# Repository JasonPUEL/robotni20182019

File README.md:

# RobotNI

Le robot aura pour nouvel objectif de chercher son chemin dans un environnement inconnu. Il devra le cartographier pour « faire des livraison/ trie de colis » en fonction de contrainte prédéfini.
Apres définition de ces contraintes le robot pourra être parfaitement autonome, bien qu’un retour d’informations vers l’utilisateur soit possible (retour vidéo/informations sur la carte découverte).
Les contraintes pourront être de chercher « colis », les trier et éventuellement de déposer les « colis » à un endroit prédéfinit.

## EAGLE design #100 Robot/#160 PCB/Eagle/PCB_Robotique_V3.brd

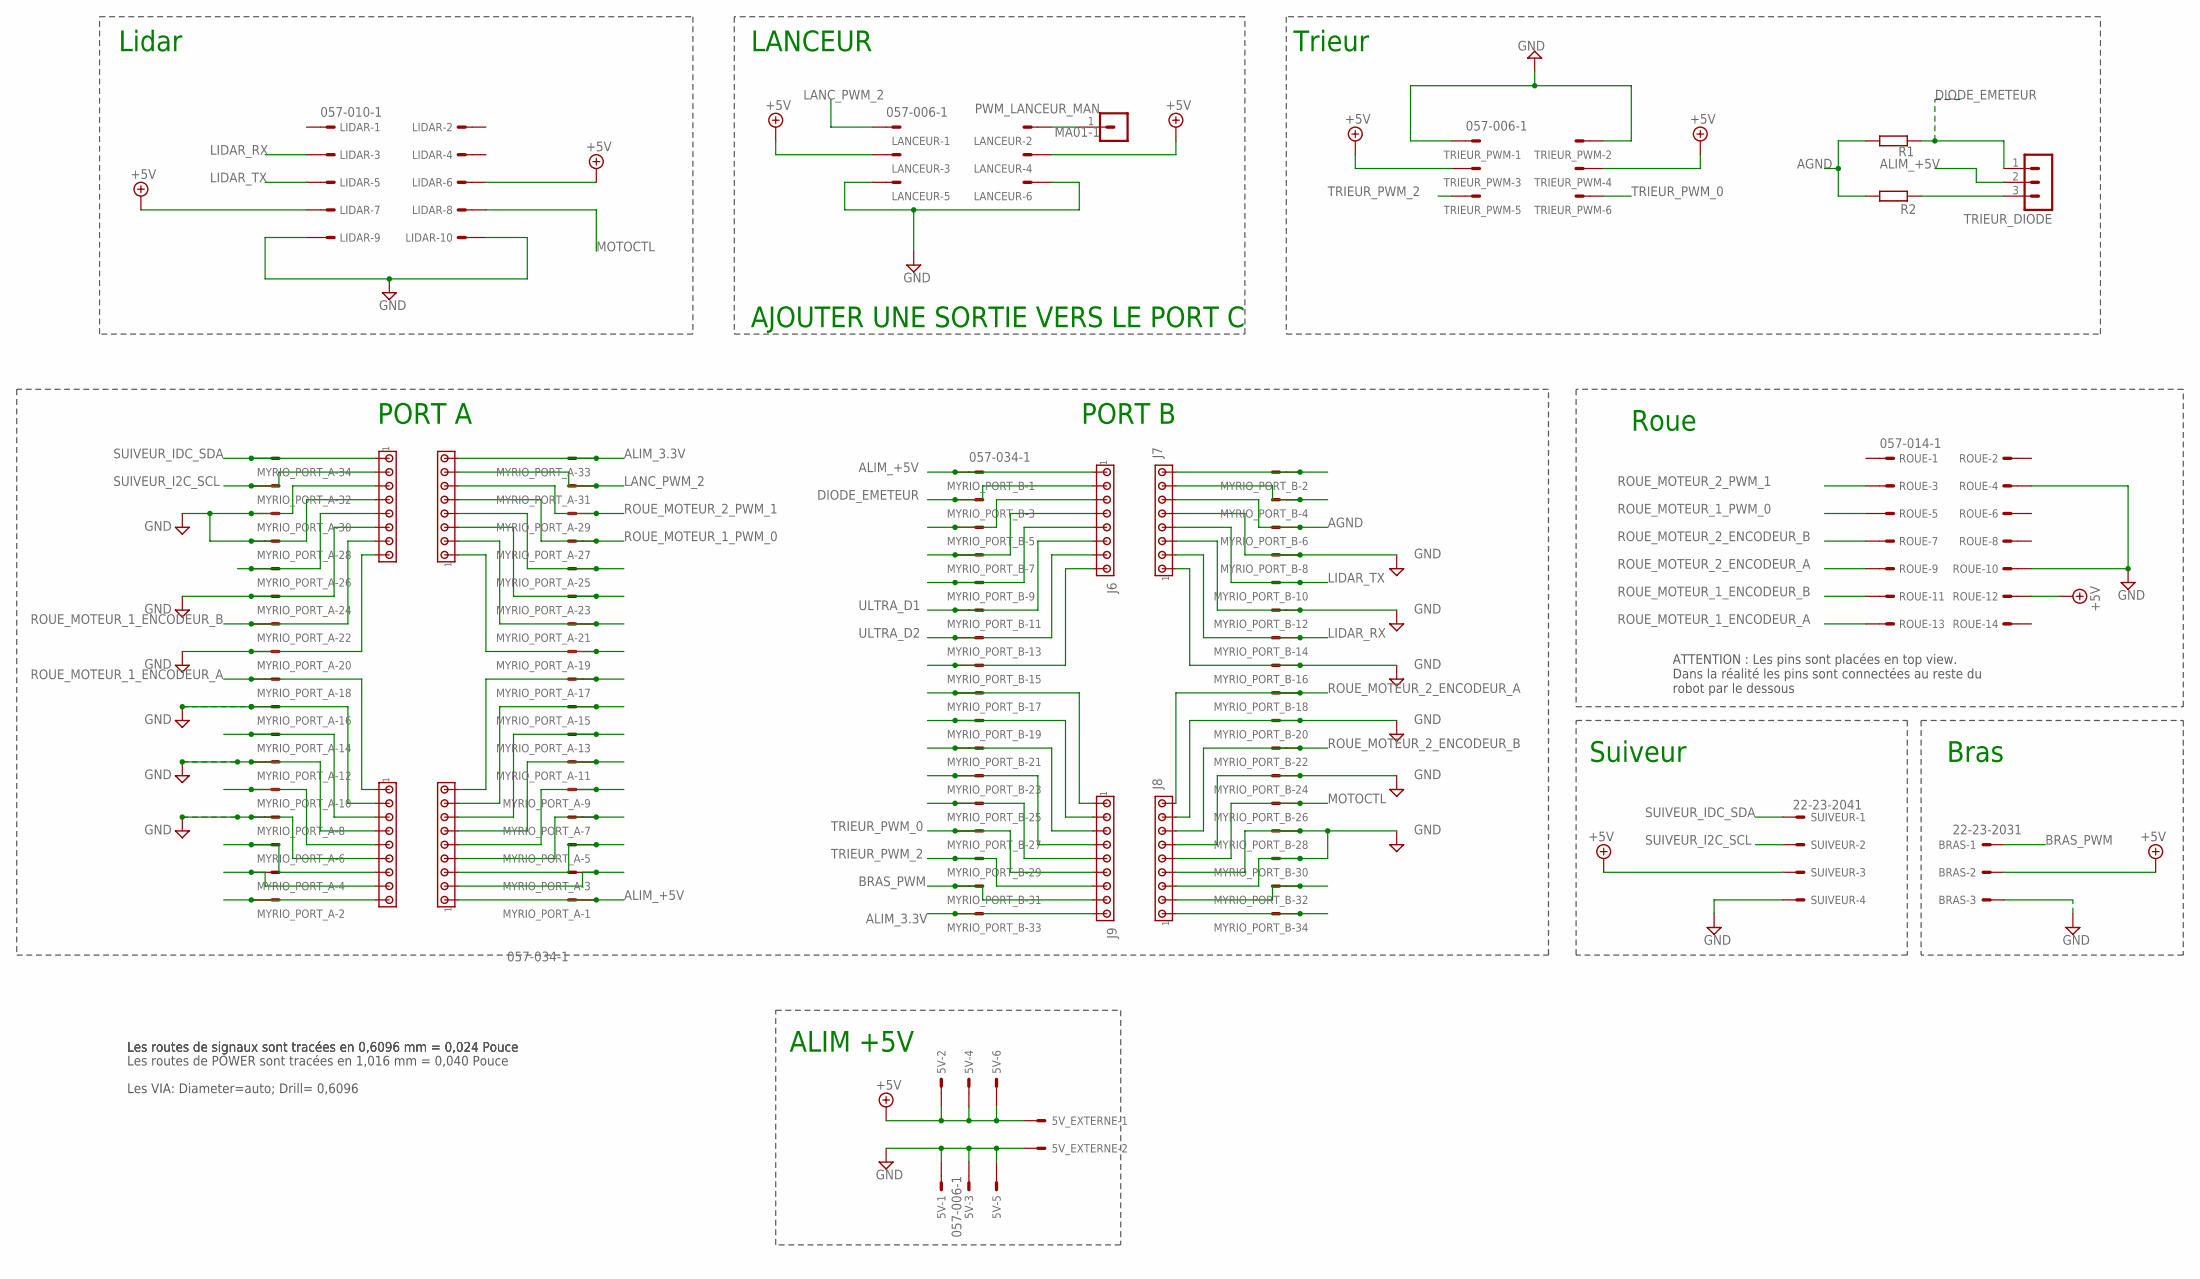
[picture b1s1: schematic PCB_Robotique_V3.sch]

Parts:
5V: 057-006-1
5V_EXTERNE: KK-156-2
BRAS: 22-23-2031
J2, J3, J6, J7: MTA08-100; 10X08MTA
J4, J5, J8, J9: MTA09-100; 10X09MTA
LANCEUR: 057-006-1
LIDAR: 057-010-1
MYRIO_PORT_A: 057-034-1
MYRIO_PORT_B: 057-034-1
PWM_LANCEUR_MAN: MA01-1
R1: 15K; R
R2: 180; R
ROUE: 057-014-1
SUIVEUR: 22-23-2041
TRIEUR_DIODE: MA03-1
TRIEUR_PWM: 057-006-1

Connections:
4B: J7.7, MYRIO_PORT_B.4
+5V: 5V.2, 5V.4, 5V.6, 5V_EXTERNE.1, BRAS.2, LANCEUR.3, LANCEUR.4, LIDAR.6, LIDAR.7, ROUE.12, SUIVEUR.3, TRIEUR_PWM.3, TRIEUR_PWM.4
AGND: J7.6, MYRIO_PORT_B.6, R1.1, R2.2
ALIM_3.3V: J3.8, J9.9, MYRIO_PORT_A.33, MYRIO_PORT_B.33
ALIM_+5V: J4.1, J6.1, MYRIO_PORT_A.1, MYRIO_PORT_B.1, TRIEUR_DIODE.2
BRAS_PWM: BRAS.1, J9.8, MYRIO_PORT_B.31
DIODE: R2.1, TRIEUR_DIODE.3
DIODE_EMETEUR: J6.2, MYRIO_PORT_B.3, R1.2, TRIEUR_DIODE.1
GND: 5V.1, 5V.3, 5V.5, 5V_EXTERNE.2, BRAS.3, J2.3, J2.4, J2.6, J2.8, J5.2, J5.4, J5.6, J7.1, J7.3, J7.5, J8.3, J8.4, J8.6, J8.8, LANCEUR.5, LANCEUR.6, LIDAR.9, LIDAR.10, MYRIO_PORT_A.8, MYRIO_PORT_A.12, MYRIO_PORT_A.16, MYRIO_PORT_A.20, MYRIO_PORT_A.24, MYRIO_PORT_A.28, MYRIO_PORT_A.30, MYRIO_PORT_B.8, MYRIO_PORT_B.12, MYRIO_PORT_B.16, MYRIO_PORT_B.20, MYRIO_PORT_B.24, MYRIO_PORT_B.28, MYRIO_PORT_B.30, ROUE.4, ROUE.10, SUIVEUR.4, TRIEUR_PWM.1, TRIEUR_PWM.2
LANC_PWM_2: J3.7, LANCEUR.1, MYRIO_PORT_A.31
LIDAR_RX: J7.2, LIDAR.3, MYRIO_PORT_B.14
LIDAR_TX: J7.4, LIDAR.5, MYRIO_PORT_B.10
MOTOCTL: J8.5, LIDAR.8, MYRIO_PORT_B.26
unnamed: J2.5, MYRIO_PORT_A.26
unnamed: J7.8, MYRIO_PORT_B.2
unnamed: J5.8, MYRIO_PORT_A.4
unnamed: J5.9, MYRIO_PORT_A.2
unnamed: J3.4, MYRIO_PORT_A.25
unnamed: J3.3, MYRIO_PORT_A.23
unnamed: J3.2, MYRIO_PORT_A.21
unnamed: J3.1, MYRIO_PORT_A.19
unnamed: J4.9, MYRIO_PORT_A.17
unnamed: J4.8, MYRIO_PORT_A.15
unnamed: J4.7, MYRIO_PORT_A.13
unnamed: J4.6, MYRIO_PORT_A.11
unnamed: J4.5, MYRIO_PORT_A.9
unnamed: J4.4, MYRIO_PORT_A.7
unnamed: J4.3, MYRIO_PORT_A.5
unnamed: J4.2, MYRIO_PORT_A.3
unnamed: J8.2, MYRIO_PORT_B.32
unnamed: J8.1, MYRIO_PORT_B.34
unnamed: J9.5, MYRIO_PORT_B.25
unnamed: J9.4, MYRIO_PORT_B.23
unnamed: J9.3, MYRIO_PORT_B.21
unnamed: J9.2, MYRIO_PORT_B.19
unnamed: J9.1, MYRIO_PORT_B.17
unnamed: J6.8, MYRIO_PORT_B.15
unnamed: J6.5, MYRIO_PORT_B.9
unnamed: J6.4, MYRIO_PORT_B.7
unnamed: J6.3, MYRIO_PORT_B.5
unnamed: J5.7, MYRIO_PORT_A.6
PWM_LANCEUR_MAN: LANCEUR.2, PWM_LANCEUR_MAN.1
ROUE_MOTEUR_1_ENCODEUR_A: J5.1, MYRIO_PORT_A.18, ROUE.13
ROUE_MOTEUR_1_ENCODEUR_B: J2.7, MYRIO_PORT_A.22, ROUE.11
ROUE_MOTEUR_1_PWM_0: J3.5, MYRIO_PORT_A.27, ROUE.5
ROUE_MOTEUR_2_ENCODEUR_A: J8.9, MYRIO_PORT_B.18, ROUE.9
ROUE_MOTEUR_2_ENCODEUR_B: J8.7, MYRIO_PORT_B.22, ROUE.7
ROUE_MOTEUR_2_PWM_1: J3.6, MYRIO_PORT_A.29, ROUE.3
SDFSDFSGD: J5.5, MYRIO_PORT_A.10
SDSSDFD: J5.3, MYRIO_PORT_A.14
SUIVEUR_I2C_SCL: J2.2, MYRIO_PORT_A.32, SUIVEUR.2
SUIVEUR_I2C_SDA: J2.1, MYRIO_PORT_A.34, SUIVEUR.1
TRIEUR_PWM_0: J9.6, MYRIO_PORT_B.27, TRIEUR_PWM.6
TRIEUR_PWM_2: J9.7, MYRIO_PORT_B.29, TRIEUR_PWM.5
ULTRA_D1: J6.6, MYRIO_PORT_B.11
ULTRA_D2: J6.7, MYRIO_PORT_B.13

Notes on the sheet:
Roue
Suiveur
PORT A
PORT B
LANCEUR
Trieur
ALIM +5V
Bras
AJOUTER UNE SORTIE VERS LE PORT C
Lidar
ATTENTION : Les pins sont placées en top view. Dans la réalité les pins sont connectées au reste du robot par le dessous
Les routes de signaux sont tracées en 0,6096 mm = 0,024 Pouce
Les VIA: Diameter=auto; Drill= 0,6096
Les routes de POWER sont tracées en 1,016 mm = 0,040 Pouce

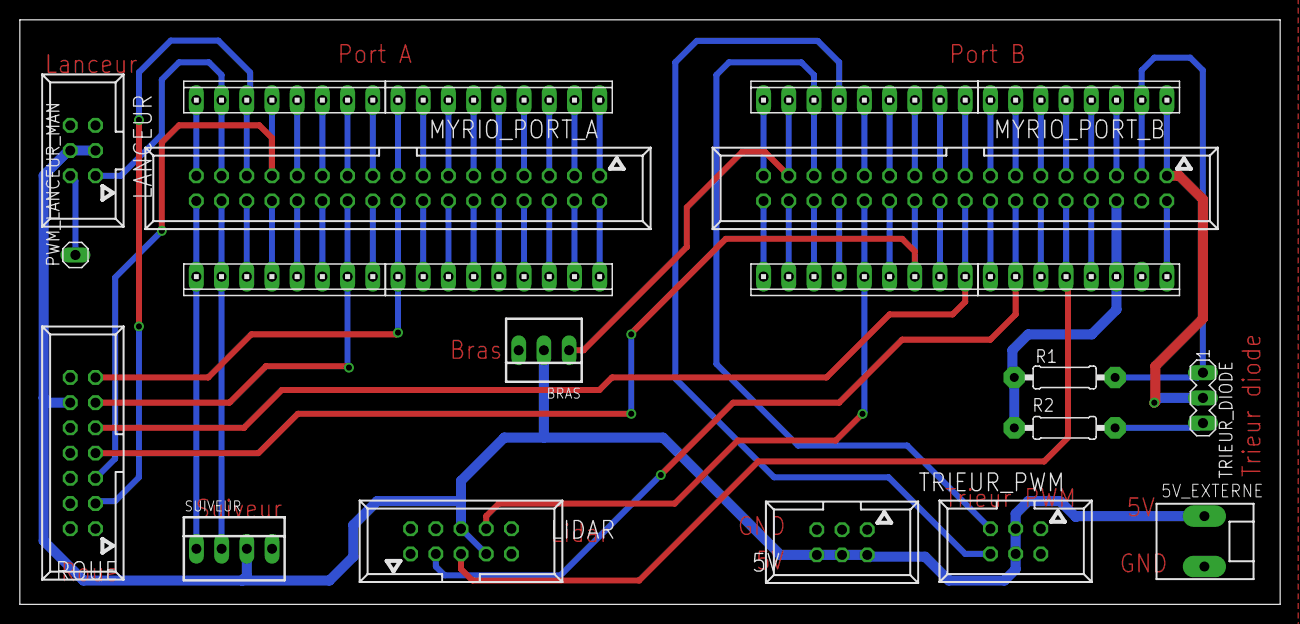
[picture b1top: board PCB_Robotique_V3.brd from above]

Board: 2 copper layers, 127.0 x 58.9 mm, 22 parts (0 on the bottom side), 56 nets.

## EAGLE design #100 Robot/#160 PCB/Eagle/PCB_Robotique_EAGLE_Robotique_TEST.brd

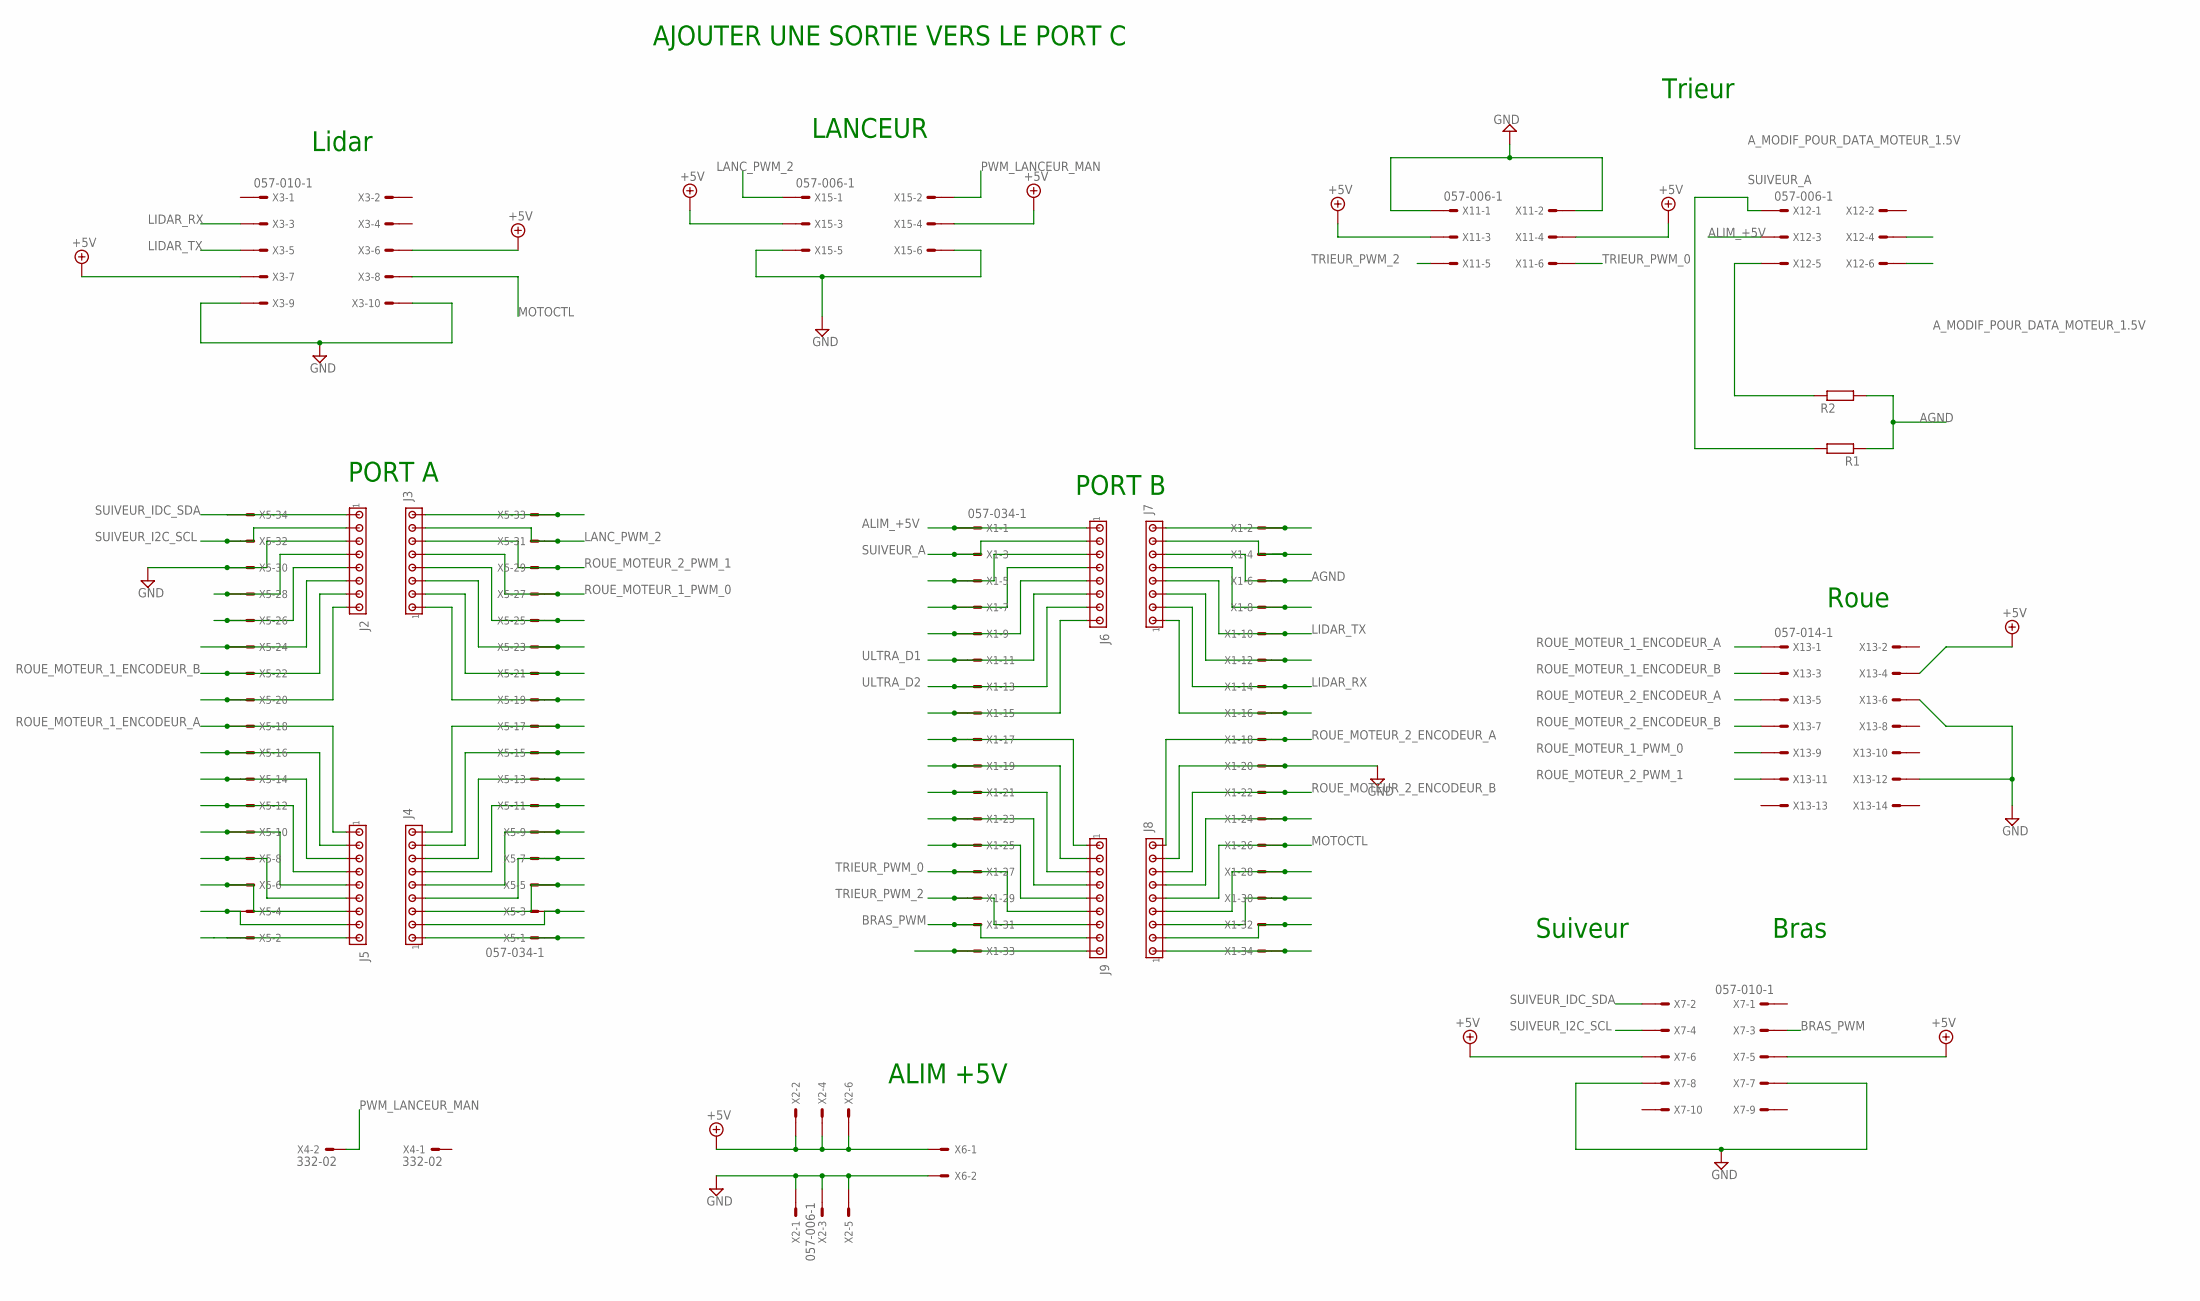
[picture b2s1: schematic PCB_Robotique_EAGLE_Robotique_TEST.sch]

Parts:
J2, J3, J6, J7: MTA08-100; 10X08MTA
J4, J5, J8, J9: MTA09-100; 10X09MTA
R1, R2: R1/4W; R
X1, X5: 057-034-1
X2, X11, X12, X15: 057-006-1
X3, X7: 057-010-1
X4: 332-02
X6: KK-156-2
X13: 057-014-1

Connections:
4B: J7.7, X1.4
+5V: X2.2, X2.4, X2.6, X3.6, X3.7, X6.1, X7.5, X7.6, X11.3, X11.4, X13.4, X15.3, X15.4
AGND: J7.6, R1.1, R2.2, X1.6
ALIM_+5V: J6.1, X1.1, X12.3
A_MODIF_POUR_DATA_MOTEUR_1.5V: R2.1, X12.5
BRAS_PWM: J9.8, X1.31, X7.3
GND: J2.3, J8.8, X1.20, X2.1, X2.3, X2.5, X3.9, X3.10, X5.30, X6.2, X7.7, X7.8, X11.1, X11.2, X13.6, X13.12, X15.5, X15.6
LANC_PWM_2: J3.7, X5.31, X15.1
LIDAR_RX: J7.2, X1.14, X3.3
LIDAR_TX: J7.4, X1.10, X3.5
MOTOCTL: J8.5, X1.26, X3.8
unnamed: J2.4, X5.28
unnamed: J2.5, X5.26
unnamed: J2.6, X5.24
unnamed: J5.2, X5.16
unnamed: J7.8, X1.2
unnamed: J5.4, X5.12
unnamed: J2.8, X5.20
unnamed: J5.6, X5.8
unnamed: J5.8, X5.4
unnamed: J5.9, X5.2
unnamed: J3.8, X5.33
unnamed: J3.4, X5.25
unnamed: J3.3, X5.23
unnamed: J3.2, X5.21
unnamed: J3.1, X5.19
unnamed: J4.9, X5.17
unnamed: J7.5, X1.8
unnamed: J7.3, X1.12
unnamed: J4.8, X5.15
unnamed: J4.7, X5.13
unnamed: J4.6, X5.11
unnamed: J4.5, X5.9
unnamed: J4.4, X5.7
unnamed: J4.3, X5.5
unnamed: J4.2, X5.3
unnamed: J4.1, X5.1
unnamed: J7.1, X1.16
unnamed: J8.6, X1.24
unnamed: J8.4, X1.28
unnamed: J8.3, X1.30
unnamed: J8.2, X1.32
unnamed: J8.1, X1.34
unnamed: J9.9, X1.33
unnamed: J9.5, X1.25
unnamed: J9.4, X1.23
unnamed: J9.3, X1.21
unnamed: J9.2, X1.19
unnamed: J9.1, X1.17
unnamed: J6.8, X1.15
unnamed: J6.5, X1.9
unnamed: J6.4, X1.7
unnamed: J6.3, X1.5
unnamed: J5.7, X5.6
PWM_LANCEUR_MAN: X4.2, X15.2
ROUE_MOTEUR_1_ENCODEUR_A: J5.1, X5.18, X13.1
ROUE_MOTEUR_1_ENCODEUR_B: J2.7, X5.22, X13.3
ROUE_MOTEUR_1_PWM_0: J3.5, X5.27, X13.9
ROUE_MOTEUR_2_ENCODEUR_A: J8.9, X1.18, X13.5
ROUE_MOTEUR_2_ENCODEUR_B: J8.7, X1.22, X13.7
ROUE_MOTEUR_2_PWM_1: J3.6, X5.29, X13.11
SDFSDFSGD: J5.5, X5.10
SDSSDFD: J5.3, X5.14
SUIVEUR_A: J6.2, R1.2, X1.3, X12.1
SUIVEUR_I2C_SCL: J2.2, X5.32, X7.4
SUIVEUR_IDC_SDA: J2.1, X5.34, X7.2
TRIEUR_PWM_0: J9.6, X1.27, X11.6
TRIEUR_PWM_2: J9.7, X1.29, X11.5
ULTRA_D1: J6.6, X1.11
ULTRA_D2: J6.7, X1.13

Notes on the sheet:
Roue
Suiveur
PORT A
PORT B
LANCEUR
Trieur
ALIM +5V
Bras
AJOUTER UNE SORTIE VERS LE PORT C
Lidar

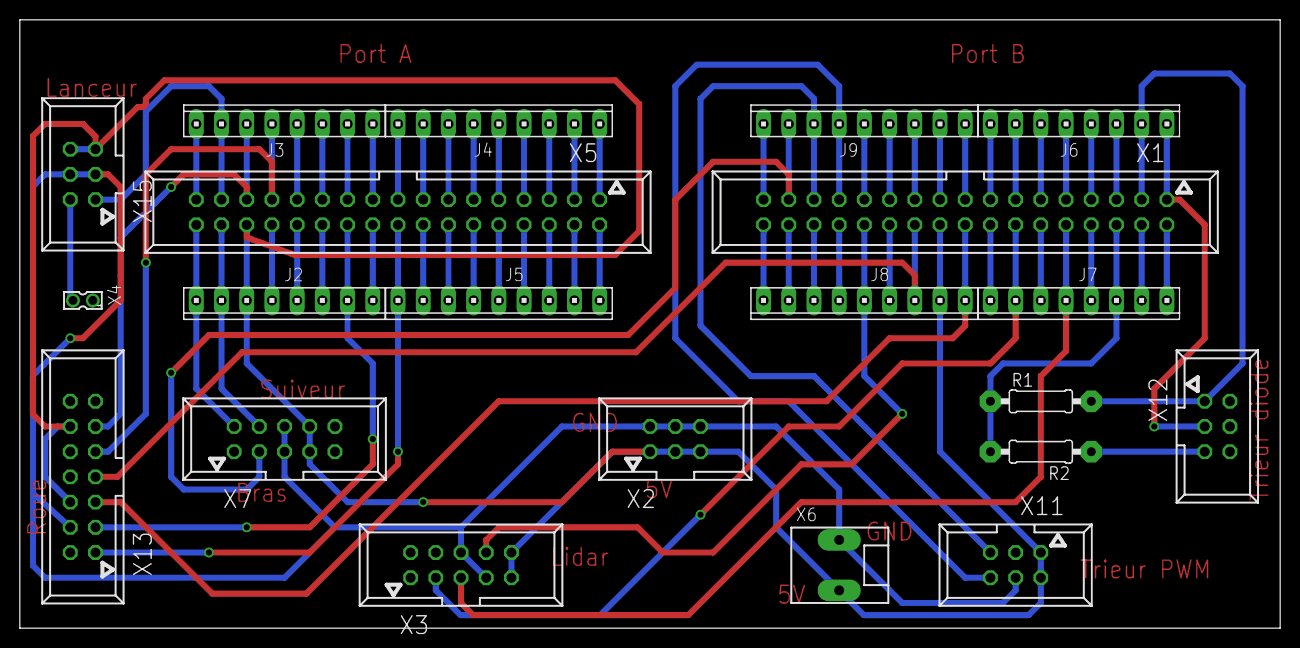
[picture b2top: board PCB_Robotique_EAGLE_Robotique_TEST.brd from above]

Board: 2 copper layers, 127.0 x 61.3 mm, 21 parts (0 on the bottom side), 70 nets.

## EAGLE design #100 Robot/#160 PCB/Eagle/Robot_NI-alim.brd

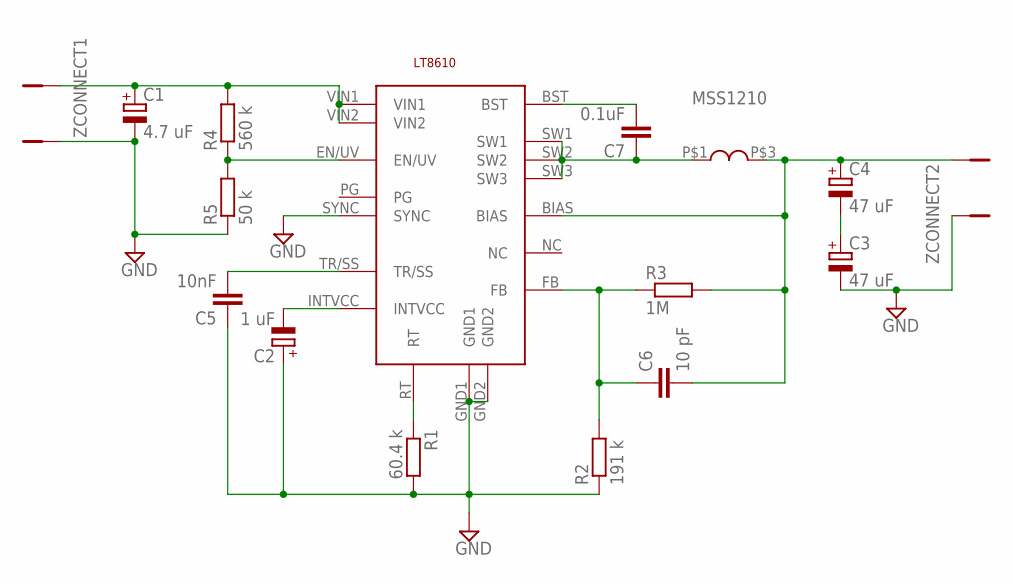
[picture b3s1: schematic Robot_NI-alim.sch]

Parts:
C1: 4.7 uF; C-POL5MM
C2: 1 uF; C-POL5MM
C3, C4: 47 uF; C-POL5MM
C5: 10nF; C0805
C6: 10 pF; C0805
C7: 0.1uF; C0805
R1: 60.4 k; R0805
R2: 191 k; R0805
R3: 1M; R0805
R4: 560 k; R0805
R5: 50 k; R0805
U$1: MSS1210
U$2: LT8610AC
ZCONNECT1, ZCONNECT2: LED5MM

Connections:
GND: C1.-, C2.+, C3.-, C5.1, R1.2, R2.1, R5.1, U$2.GND1, U$2.GND2, U$2.SYNC, ZCONNECT1.K (C), ZCONNECT2.A
unnamed: C1.+, R4.2, U$2.VIN1, U$2.VIN2, ZCONNECT1.A
unnamed: R4.1, R5.2, U$2.EN/UV
unnamed: C5.2, U$2.TR/SS
unnamed: C2.-, U$2.INTVCC
unnamed: C3.+, C4.-
unnamed: R1.1, U$2.RT
unnamed: C7.1, U$1.P$1, U$2.SW1, U$2.SW2, U$2.SW3
unnamed: C7.2, U$2.BST
unnamed: C4.+, C6.2, R3.2, U$1.P$3, U$2.BIAS, ZCONNECT2.K (C)
unnamed: C6.1, R2.2, R3.1, U$2.FB

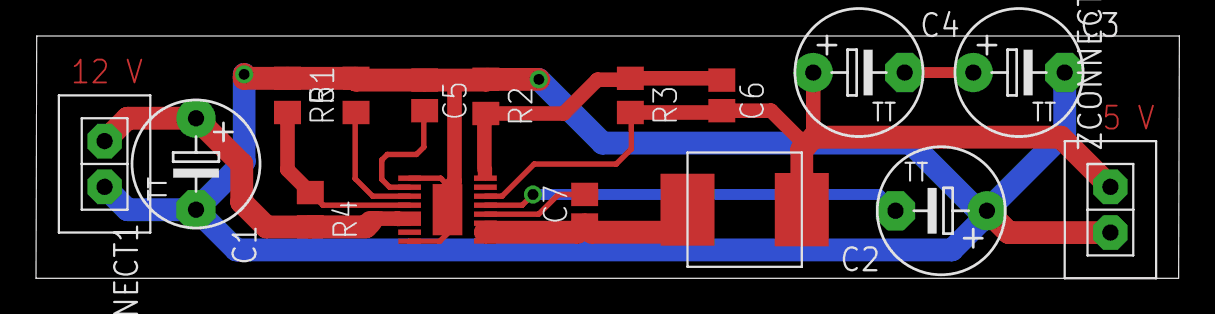
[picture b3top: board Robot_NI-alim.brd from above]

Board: 2 copper layers, 63.5 x 13.5 mm, 16 parts (0 on the bottom side), 11 nets.

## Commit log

2019-03-14 explication labview
2019-03-14 code + datasheets
2019-03-15 trieur de balles svg + code audio et video raspberry
2019-03-15 lcd library
2019-03-15 Boitier Raspberry
    Upload du fichier de découpe laser + Datasheet
2019-03-15 New Getion de fichiers
2019-03-15 Importation des fichiers M2
2019-03-21 Upload Datasheet Raspberry PI
2019-03-29 Push Regle 2018
2019-04-11 Update Weekly
2019-04-25 Update code Labview
2019-04-29 Update code Labview
    RT_Sceaux
2019-04-29 Datasheet diode + lanceur_RT
2019-04-30 Update code Ladview
2019-04-30 datasheet servo trappe
2019-05-02 RT sceaux/avance/recule/lanceur
2019-05-02 RT lanceur
2019-05-02 RT_trieur_balles
2019-05-02 update RT
2019-05-06 Doc code Labview
2019-05-09 Information Pitch
2019-05-09 sous_vi_RT_lanceur
    ajout def type enum_lanceur
2019-05-09 update virage RT
2019-05-12 RE Update code Labview
2019-05-13 Update Code Labview
    tout marche sauf trieur
2019-05-15 PCB V3 + Weekly
2019-05-16 Modification PCB_V3
2019-05-16 Gestion de projet + Pitch2 Poster
2019-05-17 maj trieur + doc diode
2019-05-17 doc servo trieur manège (360°)
2019-05-18 Poster + Brouillon Datasheet
2019-05-20 Ajout doc vi labview
2019-05-20 Update PCB V3 + Gestion de Projet
2019-05-21 update code + creation version 2018-2019
2019-05-21 RACI Semestre 2
2019-05-21 Datasheet trieur
2019-05-22 Auto stash before merge of "Dev" and "origin/Dev"
2019-05-22 Update PCB et Datasheet PCB
2019-05-22 ajout delai demarrage
2019-05-27 Upload Datasheet
2019-10-16 Auto stash before merge of "Dev" and "origin/Jason_en_Panic"
2021-04-27 Add Gitignore
